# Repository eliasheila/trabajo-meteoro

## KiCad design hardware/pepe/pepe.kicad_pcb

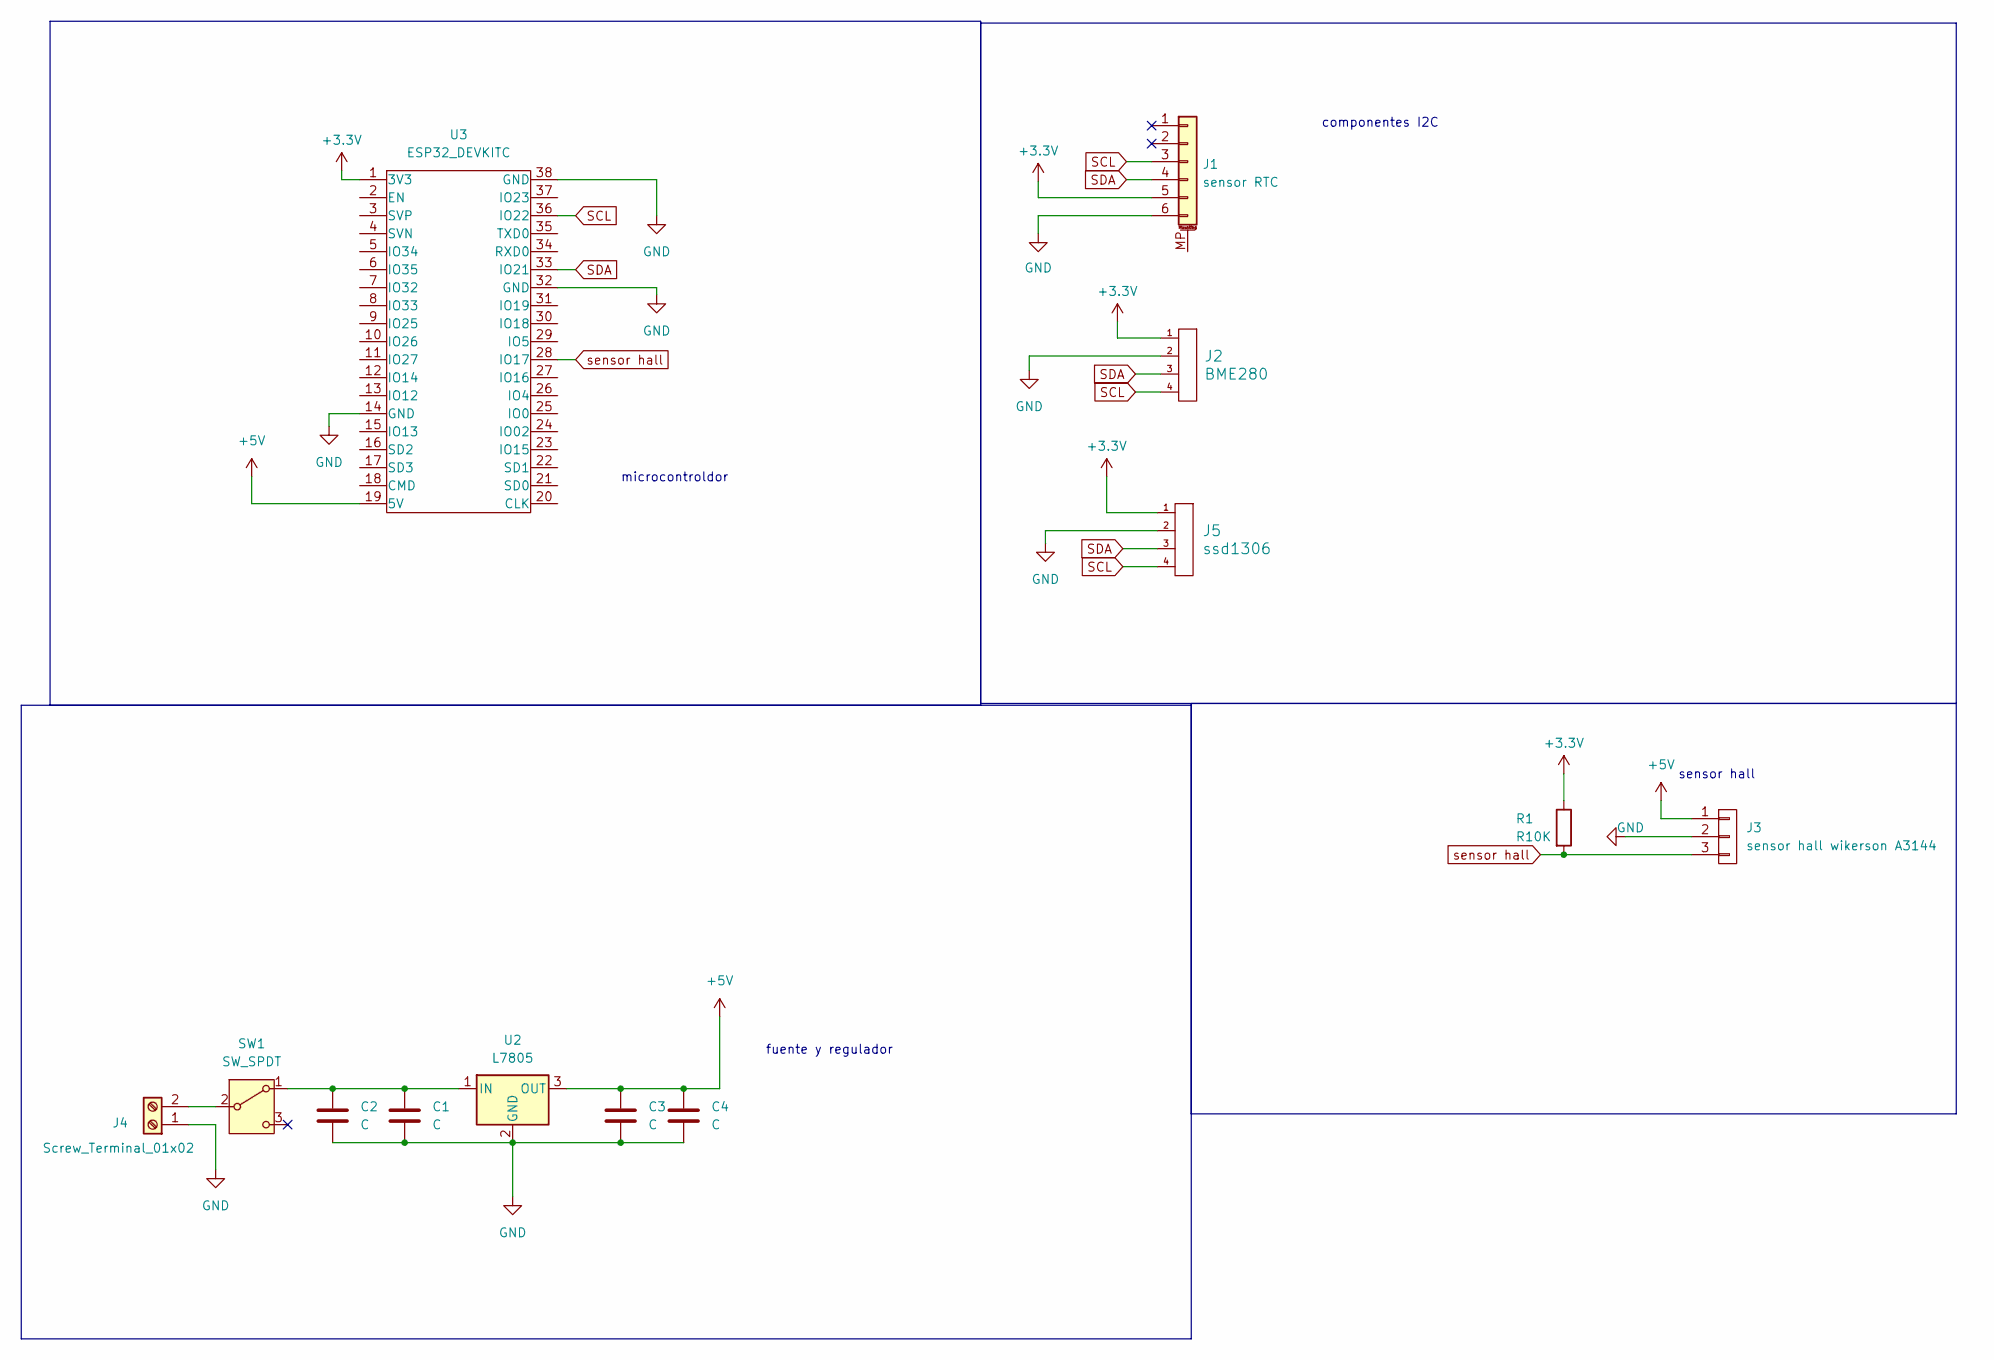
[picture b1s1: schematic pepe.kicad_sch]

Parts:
C1, C3: C; CAP_0.1
C2, C4: C; C_0805
J1: sensor RTC; Pin_Header_6
J2: BME280; pin_strip_4
J3: sensor hall wikerson A3144; Pin_Strip_3
J4: Screw_Terminal_01x02; BORNERA2_AZUL
J5: ssd1306; pin_strip_4
R1: R10K; R_0805
SW1: SW_SPDT; Pin_Header_3
U2: L7805; TO-220-3_Vertical
U3: ESP32_DEVKITC

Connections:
+3.3V: J1.5, J2.1, J5.1, R1.1, U3.1 (3V3)
+5V: C3.1, C4.1, J3.1, U2.3 (OUT), U3.19 (5V)
GND: C1.2, C2.2, C3.2, C4.2, J1.6, J2.2, J3.2, J4.1, J5.2, U2.2 (GND), U3.14 (GND), U3.32 (GND), U3.38 (GND)
unnamed: J4.2, SW1.2 (B)
unnamed: C1.1, C2.1, SW1.1 (A), U2.1 (IN)
SCL: J1.3, J2.4, J5.4, U3.36 (IO22)
SDA: J1.4, J2.3, J5.3, U3.33 (IO21)
sensor hall: J3.3, R1.2, U3.28 (IO17)

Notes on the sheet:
microcontroldor
fuente y regulador
componentes I2C
sensor hall

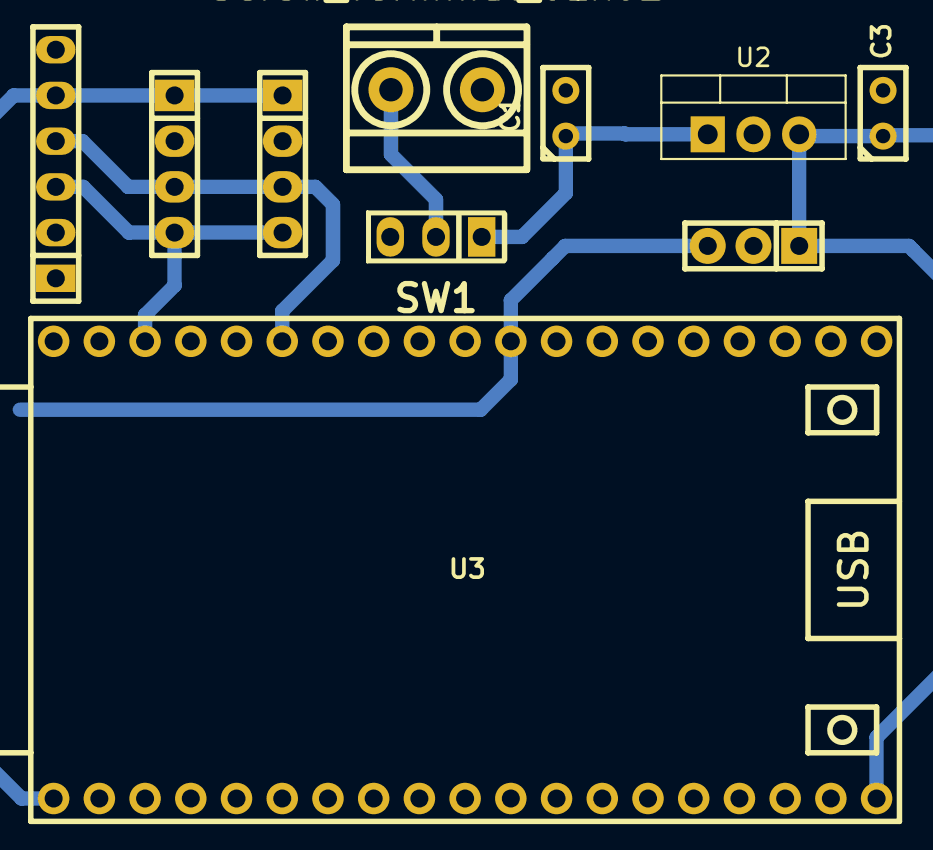
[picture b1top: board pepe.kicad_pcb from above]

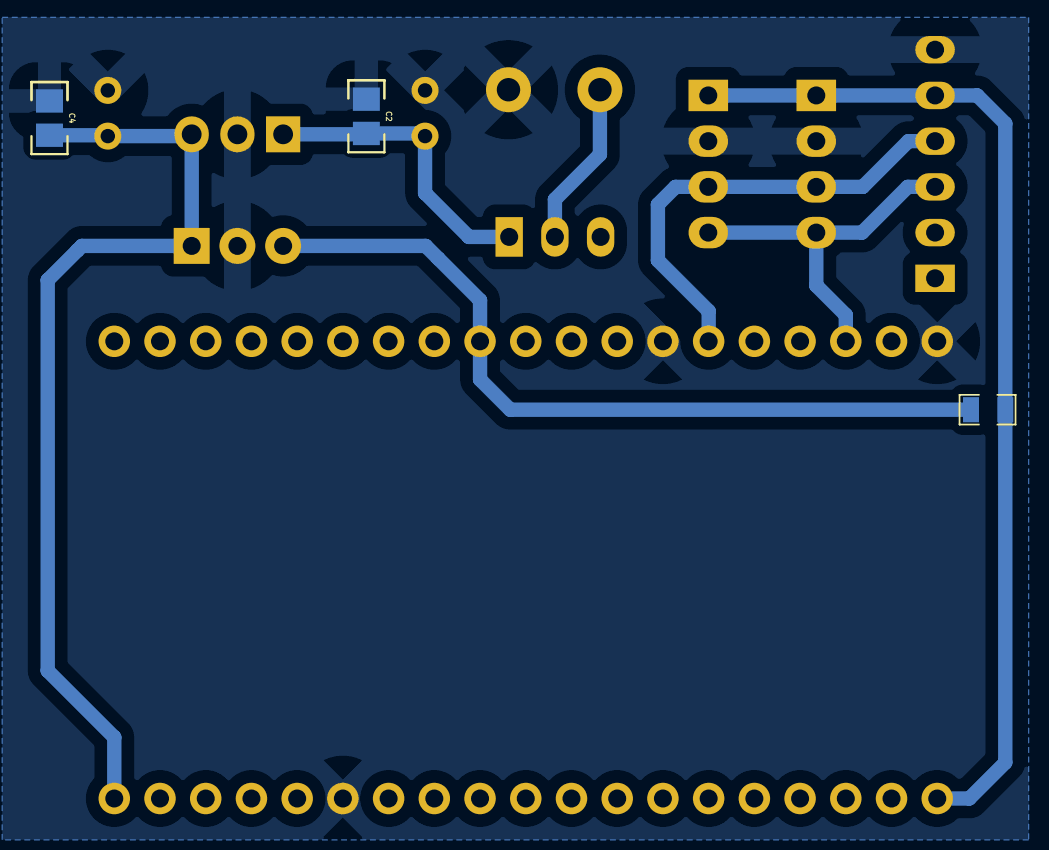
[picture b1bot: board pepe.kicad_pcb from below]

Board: 2 copper layers, 13 parts (3 on the bottom side), 8 nets.
